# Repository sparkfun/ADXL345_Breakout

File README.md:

ADXL345 Breakout Board
===============================

[
*ADXL345 Breakout Board (SEN-09836)*](https://www.sparkfun.com/products/9836)

The ADXL345 is a small, thin, low power, 3-axis MEMS accelerometer with high resolution 913-bit) measurement at up to +-16g. 
Digital output data is formatted as 16-bit twos complement and is accessible through either an SPI or I2C digital interface. 

Repository Contents
-------------------

* **/Hardware** - All Eagle design files (.brd, .sch, .STL)
* **/Libraries** - All Arduino libraries and board examples
* **/Production** - Test bed files and production panel files

License Information
-------------------
The hardware is released under [Creative Commons ShareAlike 4.0 International](https://creativecommons.org/licenses/by-sa/4.0/).
The code is beerware; if you see me (or any other SparkFun employee) at the local, and you've found our code helpful, please buy us a round!

Distributed as-is; no warranty is given.

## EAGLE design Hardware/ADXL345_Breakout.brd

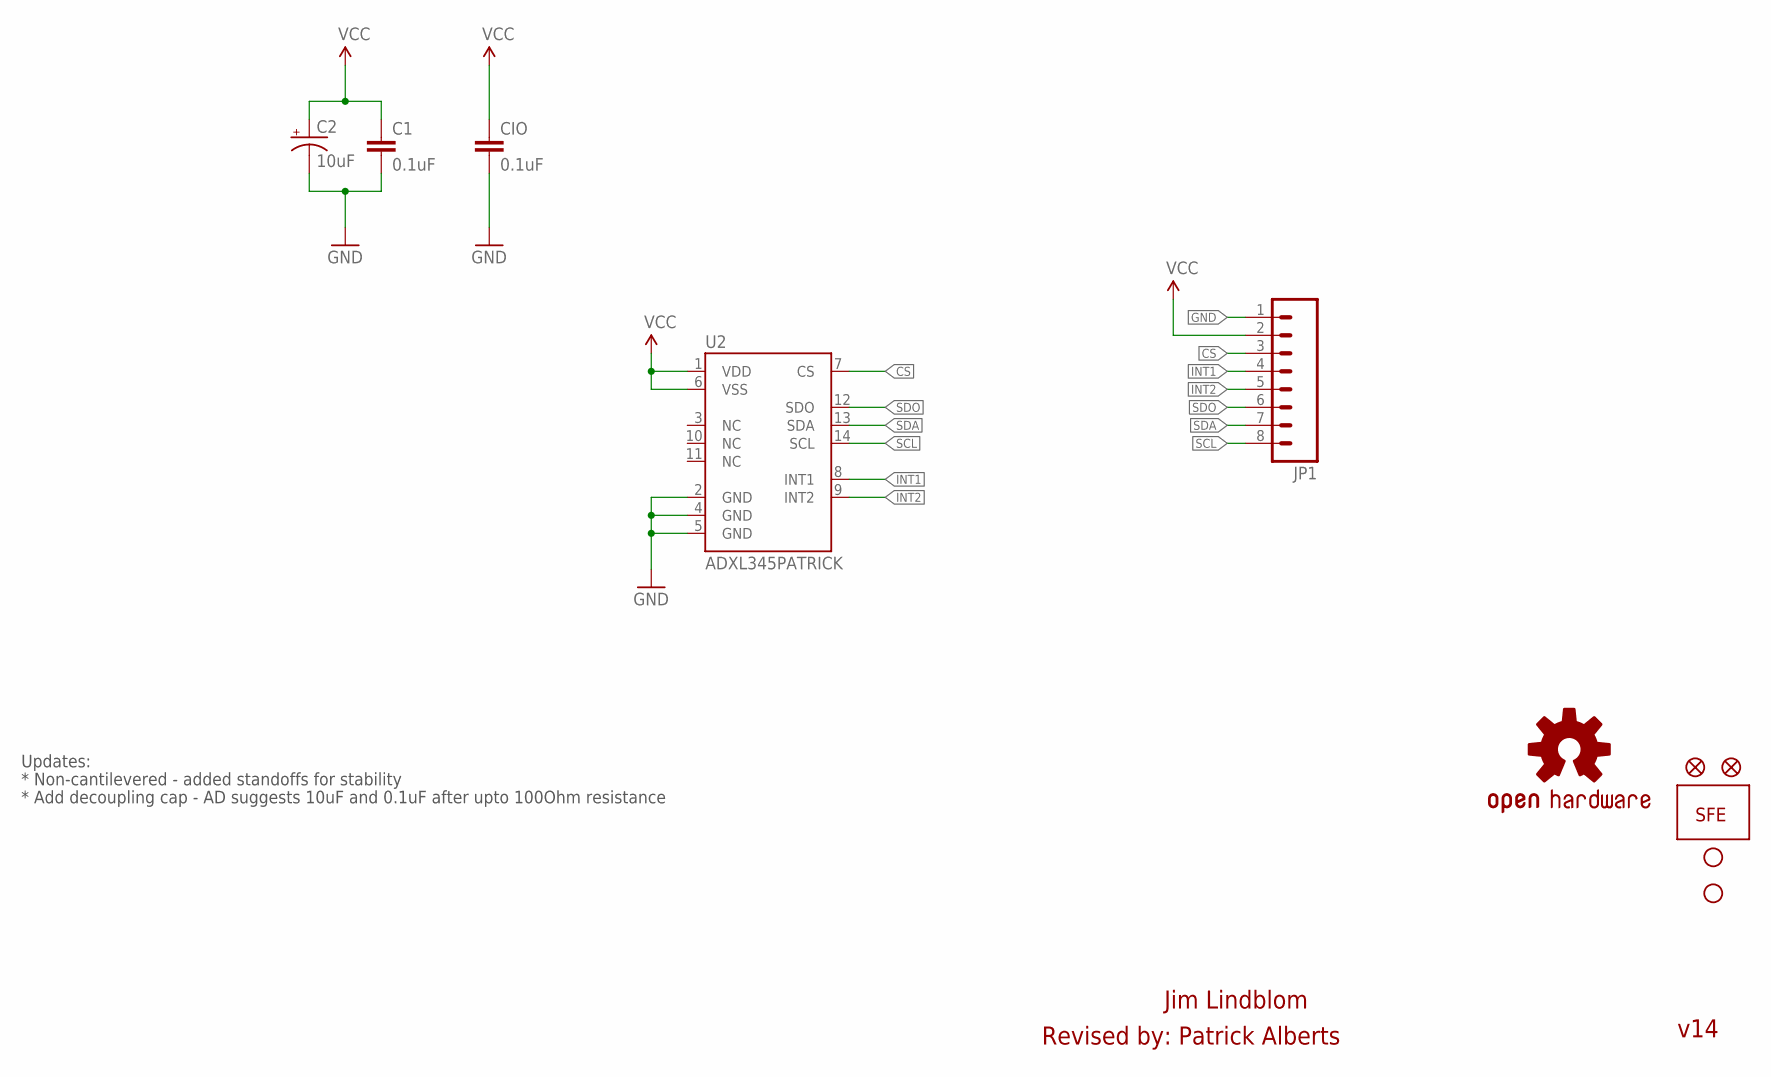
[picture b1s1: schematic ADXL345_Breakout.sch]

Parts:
C1: 0.1uF; 0603-CAP
C2: 10uF; EIA3216
CIO: 0.1uF; 0603-CAP
JP1: M08; 1X08
JP2, JP3: STAND-OFF
JP4, JP5: FIDUCIAL1X2; FIDUCIAL-1X2
U2: ADXL345PATRICK; LGA14_1:1_PATRICK
U$2: LOGO-SFENEW; SFE-NEW-WEBLOGO
U$3: OSHW-LOGOS; OSHW-LOGO-S

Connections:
CS: JP1.3, U2.7 (CS)
GND: C1.2, C2.C (-), CIO.2, JP1.1, U2.2 (GND), U2.4 (GND), U2.5 (GND)
INT1: JP1.4, U2.8 (INT1)
INT2: JP1.5, U2.9 (INT2)
SCL: JP1.8, U2.14 (SCL)
SDA: JP1.7, U2.13 (SDA)
SDO: JP1.6, U2.12 (SDO)
VCC: C1.1, C2.A (+), CIO.1, JP1.2, U2.1 (VDD), U2.6 (VSS)

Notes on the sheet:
Updates:
* Non-cantilevered - added standoffs for stability
* Add decoupling cap - AD suggests 10uF and 0.1uF after upto 100Ohm resistance
Jim Lindblom
Revised by: Patrick Alberts
v14

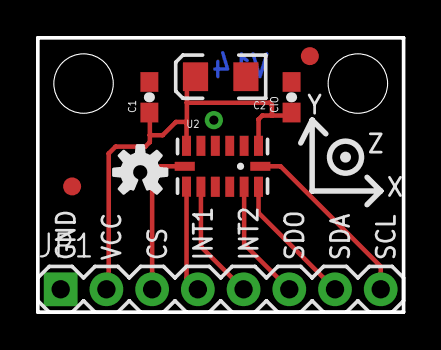
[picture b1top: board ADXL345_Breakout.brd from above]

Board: 2 copper layers, 20.3 x 15.2 mm, 11 parts (1 on the bottom side), 8 nets.

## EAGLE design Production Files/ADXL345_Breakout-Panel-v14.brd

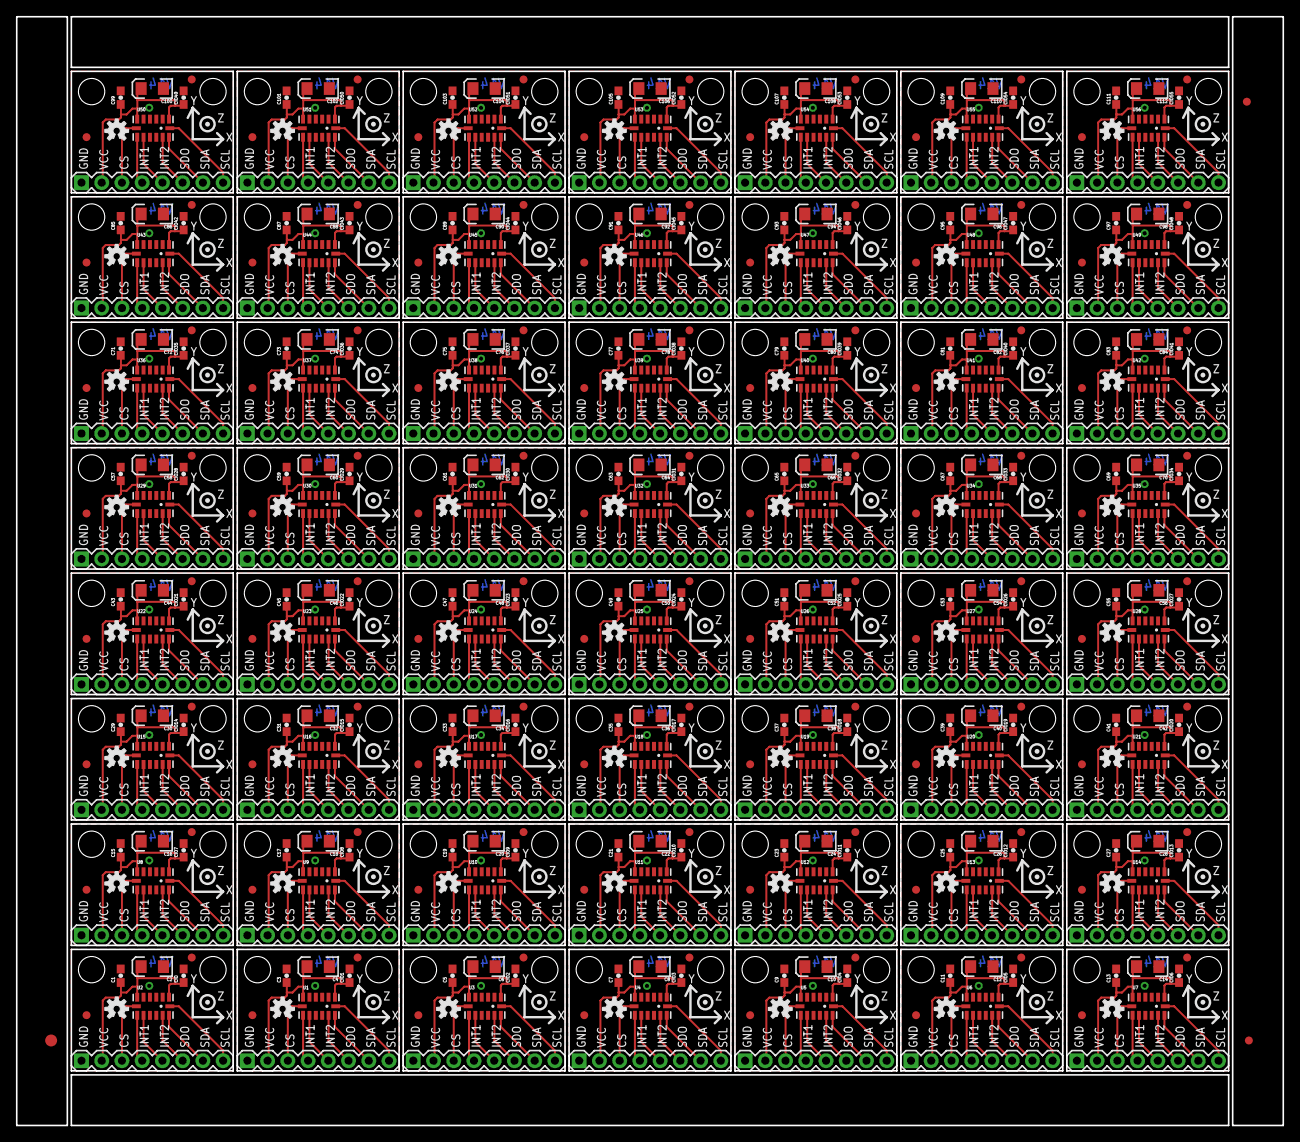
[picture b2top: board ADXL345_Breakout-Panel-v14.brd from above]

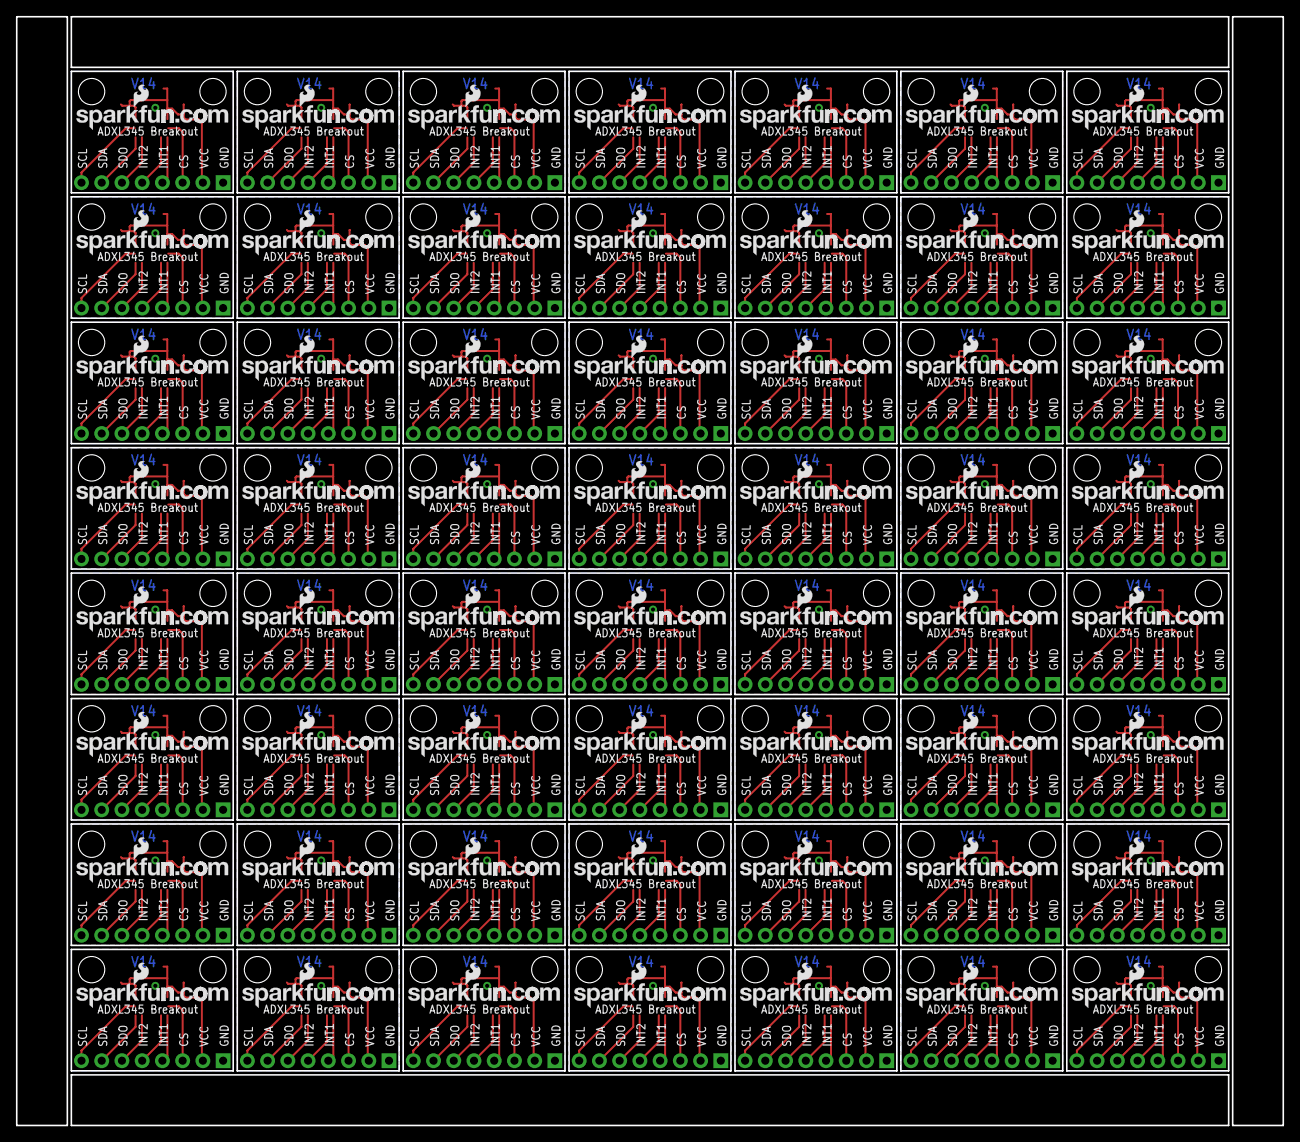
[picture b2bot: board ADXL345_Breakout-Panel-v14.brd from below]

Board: 2 copper layers, 159.0 x 139.2 mm, 619 parts (56 on the bottom side), 448 nets.

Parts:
C1, C3, C5, C7, C9, C11, C13, C15, C17, C19, C21, C23, C25, C27, C29, C31, C33, C35, C37, C39, C41, C43, C45, C47, C49, C51, C53, C55, C57, C59, C61, C63, C65, C67, C69, C71, C73, C75, C77, C79, C81, C83, C85, C87, C89, C91, C93, C95, C97, C99, C101, C103, C105, C107, C109, C111: 0.1uF; 0603-CAP
C2, C4, C6, C8, C10, C12, C14, C16, C18, C20, C22, C24, C26, C28, C30, C32, C34, C36, C38, C40, C42, C44, C46, C48, C50, C52, C54, C56, C58, C60, C62, C64, C66, C68, C70, C72, C74, C76, C78, C80, C82, C84, C86, C88, C90, C92, C94, C96, C98, C100, C102, C104, C106, C108, C110, C112: 10uF; EIA3216
CIO, CIO1, CIO2, CIO3, CIO4, CIO5, CIO6, CIO7, CIO8, CIO9, CIO10, CIO11, CIO12, CIO13, CIO14, CIO15, CIO16, CIO17, CIO18, CIO19, CIO20, CIO21, CIO22, CIO23, CIO24, CIO25, CIO26, CIO27, CIO28, CIO29, CIO30, CIO31, CIO32, CIO33, CIO34, CIO35, CIO36, CIO37, CIO38, CIO39, CIO40, CIO41, CIO42, CIO43, CIO44, CIO45, CIO46, CIO47, CIO48, CIO49, CIO50, CIO51, CIO52, CIO53, CIO54, CIO55: 0.1uF; 0603-CAP
E$1: FIDUCIAL-1.5X3
E$4, E$6: FIDUCIAL-1X2
JP1, JP6, JP11, JP16, JP21, JP26, JP31, JP36, JP41, JP46, JP51, JP56, JP61, JP66, JP71, JP76, JP81, JP86, JP91, JP96, JP101, JP106, JP111, JP116, JP121, JP126, JP131, JP136, JP141, JP146, JP151, JP156, JP161, JP166, JP171, JP176, JP181, JP186, JP191, JP196, JP201, JP206, JP211, JP216, JP221, JP226, JP231, JP236, JP241, JP246, JP251, JP256, JP261, JP266, JP271, JP276: 1X08
JP2, JP3, JP7, JP8, JP12, JP13, JP17, JP18, JP22, JP23, JP27, JP28, JP32, JP33, JP37, JP38, JP42, JP43, JP47, JP48, JP52, JP53, JP57, JP58, JP62, JP63, JP67, JP68, JP72, JP73, JP77, JP78, JP82, JP83, JP87, JP88, JP92, JP93, JP97, JP98, JP102, JP103, JP107, JP108, JP112, JP113, JP117, JP118, JP122, JP123, JP127, JP128, JP132, JP133, JP137, JP138, JP142, JP143, JP147, JP148, JP152, JP153, JP157, JP158, JP162, JP163, JP167, JP168, JP172, JP173, JP177, JP178, JP182, JP183, JP187, JP188, JP192, JP193, JP197, JP198, JP202, JP203, JP207, JP208, JP212, JP213, JP217, JP218, JP222, JP223, JP227, JP228, JP232, JP233, JP237, JP238, JP242, JP243, JP247, JP248, JP252, JP253, JP257, JP258, JP262, JP263, JP267, JP268, JP272, JP273, JP277, JP278: STAND-OFF
JP4, JP5, JP9, JP10, JP14, JP15, JP19, JP20, JP24, JP25, JP29, JP30, JP34, JP35, JP39, JP40, JP44, JP45, JP49, JP50, JP54, JP55, JP59, JP60, JP64, JP65, JP69, JP70, JP74, JP75, JP79, JP80, JP84, JP85, JP89, JP90, JP94, JP95, JP99, JP100, JP104, JP105, JP109, JP110, JP114, JP115, JP119, JP120, JP124, JP125, JP129, JP130, JP134, JP135, JP139, JP140, JP144, JP145, JP149, JP150, JP154, JP155, JP159, JP160, JP164, JP165, JP169, JP170, JP174, JP175, JP179, JP180, JP184, JP185, JP189, JP190, JP194, JP195, JP199, JP200, JP204, JP205, JP209, JP210, JP214, JP215, JP219, JP220, JP224, JP225, JP229, JP230, JP234, JP235, JP239, JP240, JP244, JP245, JP249, JP250, JP254, JP255, JP259, JP260, JP264, JP265, JP269, JP270, JP274, JP275, JP279, JP280: FIDUCIAL1X2; FIDUCIAL-1X2
U1, U2, U3, U4, U5, U6, U7, U8, U9, U10, U11, U12, U13, U14, U15, U16, U17, U18, U19, U20, U21, U22, U23, U24, U25, U26, U27, U28, U29, U30, U31, U32, U33, U34, U35, U36, U37, U38, U39, U40, U41, U42, U43, U44, U45, U46, U47, U48, U49, U50, U51, U52, U53, U54, U55, U56: ADXL345PATRICK; LGA14_1:1_PATRICK
U$1, U$2, U$5, U$7, U$9, U$11, U$13, U$15, U$17, U$19, U$21, U$23, U$25, U$27, U$29, U$31, U$33, U$35, U$37, U$39, U$41, U$43, U$45, U$47, U$49, U$51, U$53, U$55, U$57, U$59, U$61, U$63, U$65, U$67, U$69, U$71, U$73, U$75, U$77, U$79, U$81, U$83, U$85, U$87, U$89, U$91, U$93, U$95, U$97, U$99, U$101, U$103, U$105, U$107, U$109, U$111: LOGO-SFENEW; SFE-NEW-WEBLOGO
U$3, U$4, U$6, U$8, U$10, U$12, U$14, U$16, U$18, U$20, U$22, U$24, U$26, U$28, U$30, U$32, U$34, U$36, U$38, U$40, U$42, U$44, U$46, U$48, U$50, U$52, U$54, U$56, U$58, U$60, U$62, U$64, U$66, U$68, U$70, U$72, U$74, U$76, U$78, U$80, U$82, U$84, U$86, U$88, U$90, U$92, U$94, U$96, U$98, U$100, U$102, U$104, U$106, U$108, U$110, U$112: OSHW-LOGOS; OSHW-LOGO-S

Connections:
CS: JP1.3, U2.7
CS1: JP6.3, U1.7
CS2: JP11.3, U3.7
CS3: JP16.3, U4.7
CS4: JP21.3, U5.7
CS5: JP26.3, U6.7
CS6: JP31.3, U7.7
CS7: JP36.3, U8.7
CS8: JP41.3, U9.7
CS9: JP46.3, U10.7
CS10: JP51.3, U11.7
CS11: JP56.3, U12.7
CS12: JP61.3, U13.7
CS13: JP66.3, U14.7
CS14: JP71.3, U15.7
CS15: JP76.3, U16.7
CS16: JP81.3, U17.7
CS17: JP86.3, U18.7
CS18: JP91.3, U19.7
CS19: JP96.3, U20.7
CS20: JP101.3, U21.7
CS21: JP106.3, U22.7
CS22: JP111.3, U23.7
CS23: JP116.3, U24.7
CS24: JP121.3, U25.7
CS25: JP126.3, U26.7
CS26: JP131.3, U27.7
CS27: JP136.3, U28.7
CS28: JP141.3, U29.7
CS29: JP146.3, U30.7
CS30: JP151.3, U31.7
CS31: JP156.3, U32.7
CS32: JP161.3, U33.7
CS33: JP166.3, U34.7
CS34: JP171.3, U35.7
CS35: JP176.3, U36.7
CS36: JP181.3, U37.7
CS37: JP186.3, U38.7
CS38: JP191.3, U39.7
CS39: JP196.3, U40.7
CS40: JP201.3, U41.7
CS41: JP206.3, U42.7
CS42: JP211.3, U43.7
CS43: JP216.3, U44.7
CS44: JP221.3, U45.7
CS45: JP226.3, U46.7
CS46: JP231.3, U47.7
CS47: JP236.3, U48.7
CS48: JP241.3, U49.7
CS49: JP246.3, U50.7
CS50: JP251.3, U51.7
CS51: JP256.3, U52.7
CS52: JP261.3, U53.7
CS53: JP266.3, U54.7
CS54: JP271.3, U55.7
CS55: JP276.3, U56.7
GND: C1.2, C2.C, CIO.2, JP1.1, U2.2, U2.4, U2.5
GND1: C3.2, C4.C, CIO1.2, JP6.1, U1.2, U1.4, U1.5
GND2: C5.2, C6.C, CIO2.2, JP11.1, U3.2, U3.4, U3.5
GND3: C7.2, C8.C, CIO3.2, JP16.1, U4.2, U4.4, U4.5
GND4: C9.2, C10.C, CIO4.2, JP21.1, U5.2, U5.4, U5.5
GND5: C11.2, C12.C, CIO5.2, JP26.1, U6.2, U6.4, U6.5
GND6: C13.2, C14.C, CIO6.2, JP31.1, U7.2, U7.4, U7.5
GND7: C15.2, C16.C, CIO7.2, JP36.1, U8.2, U8.4, U8.5
GND8: C17.2, C18.C, CIO8.2, JP41.1, U9.2, U9.4, U9.5
GND9: C19.2, C20.C, CIO9.2, JP46.1, U10.2, U10.4, U10.5
GND10: C21.2, C22.C, CIO10.2, JP51.1, U11.2, U11.4, U11.5
GND11: C23.2, C24.C, CIO11.2, JP56.1, U12.2, U12.4, U12.5
GND12: C25.2, C26.C, CIO12.2, JP61.1, U13.2, U13.4, U13.5
GND13: C27.2, C28.C, CIO13.2, JP66.1, U14.2, U14.4, U14.5
GND14: C29.2, C30.C, CIO14.2, JP71.1, U15.2, U15.4, U15.5
GND15: C31.2, C32.C, CIO15.2, JP76.1, U16.2, U16.4, U16.5
GND16: C33.2, C34.C, CIO16.2, JP81.1, U17.2, U17.4, U17.5
GND17: C35.2, C36.C, CIO17.2, JP86.1, U18.2, U18.4, U18.5
GND18: C37.2, C38.C, CIO18.2, JP91.1, U19.2, U19.4, U19.5
GND19: C39.2, C40.C, CIO19.2, JP96.1, U20.2, U20.4, U20.5
GND20: C41.2, C42.C, CIO20.2, JP101.1, U21.2, U21.4, U21.5
GND21: C43.2, C44.C, CIO21.2, JP106.1, U22.2, U22.4, U22.5
GND22: C45.2, C46.C, CIO22.2, JP111.1, U23.2, U23.4, U23.5
GND23: C47.2, C48.C, CIO23.2, JP116.1, U24.2, U24.4, U24.5
GND24: C49.2, C50.C, CIO24.2, JP121.1, U25.2, U25.4, U25.5
GND25: C51.2, C52.C, CIO25.2, JP126.1, U26.2, U26.4, U26.5
GND26: C53.2, C54.C, CIO26.2, JP131.1, U27.2, U27.4, U27.5
GND27: C55.2, C56.C, CIO27.2, JP136.1, U28.2, U28.4, U28.5
GND28: C57.2, C58.C, CIO28.2, JP141.1, U29.2, U29.4, U29.5
GND29: C59.2, C60.C, CIO29.2, JP146.1, U30.2, U30.4, U30.5
GND30: C61.2, C62.C, CIO30.2, JP151.1, U31.2, U31.4, U31.5
GND31: C63.2, C64.C, CIO31.2, JP156.1, U32.2, U32.4, U32.5
GND32: C65.2, C66.C, CIO32.2, JP161.1, U33.2, U33.4, U33.5
GND33: C67.2, C68.C, CIO33.2, JP166.1, U34.2, U34.4, U34.5
GND34: C69.2, C70.C, CIO34.2, JP171.1, U35.2, U35.4, U35.5
GND35: C71.2, C72.C, CIO35.2, JP176.1, U36.2, U36.4, U36.5
GND36: C73.2, C74.C, CIO36.2, JP181.1, U37.2, U37.4, U37.5
GND37: C75.2, C76.C, CIO37.2, JP186.1, U38.2, U38.4, U38.5
GND38: C77.2, C78.C, CIO38.2, JP191.1, U39.2, U39.4, U39.5
GND39: C79.2, C80.C, CIO39.2, JP196.1, U40.2, U40.4, U40.5
GND40: C81.2, C82.C, CIO40.2, JP201.1, U41.2, U41.4, U41.5
GND41: C83.2, C84.C, CIO41.2, JP206.1, U42.2, U42.4, U42.5
GND42: C85.2, C86.C, CIO42.2, JP211.1, U43.2, U43.4, U43.5
GND43: C87.2, C88.C, CIO43.2, JP216.1, U44.2, U44.4, U44.5
GND44: C89.2, C90.C, CIO44.2, JP221.1, U45.2, U45.4, U45.5
GND45: C91.2, C92.C, CIO45.2, JP226.1, U46.2, U46.4, U46.5
GND46: C93.2, C94.C, CIO46.2, JP231.1, U47.2, U47.4, U47.5
GND47: C95.2, C96.C, CIO47.2, JP236.1, U48.2, U48.4, U48.5
GND48: C97.2, C98.C, CIO48.2, JP241.1, U49.2, U49.4, U49.5
GND49: C99.2, C100.C, CIO49.2, JP246.1, U50.2, U50.4, U50.5
GND50: C101.2, C102.C, CIO50.2, JP251.1, U51.2, U51.4, U51.5
GND51: C103.2, C104.C, CIO51.2, JP256.1, U52.2, U52.4, U52.5
GND52: C105.2, C106.C, CIO52.2, JP261.1, U53.2, U53.4, U53.5
GND53: C107.2, C108.C, CIO53.2, JP266.1, U54.2, U54.4, U54.5
GND54: C109.2, C110.C, CIO54.2, JP271.1, U55.2, U55.4, U55.5
GND55: C111.2, C112.C, CIO55.2, JP276.1, U56.2, U56.4, U56.5
INT1: JP1.4, U2.8
INT2: JP1.5, U2.9
INT3: JP6.5, U1.9
INT4: JP6.4, U1.8
INT5: JP11.5, U3.9
INT6: JP11.4, U3.8
INT7: JP16.5, U4.9
INT8: JP16.4, U4.8
INT9: JP21.5, U5.9
INT10: JP21.4, U5.8
INT11: JP26.5, U6.9
INT12: JP26.4, U6.8
INT13: JP31.5, U7.9
INT14: JP31.4, U7.8
INT15: JP36.5, U8.9
INT16: JP36.4, U8.8
INT17: JP41.5, U9.9
INT18: JP41.4, U9.8
INT19: JP46.5, U10.9
INT20: JP46.4, U10.8
INT21: JP51.5, U11.9
INT22: JP51.4, U11.8
INT23: JP56.5, U12.9
INT24: JP56.4, U12.8
INT25: JP61.5, U13.9
INT26: JP61.4, U13.8
INT27: JP66.5, U14.9
INT28: JP66.4, U14.8
INT29: JP71.5, U15.9
INT30: JP71.4, U15.8
INT31: JP76.5, U16.9
INT32: JP76.4, U16.8
INT33: JP81.5, U17.9
INT34: JP81.4, U17.8
INT35: JP86.5, U18.9
INT36: JP86.4, U18.8
INT37: JP91.5, U19.9
INT38: JP91.4, U19.8
INT39: JP96.5, U20.9
INT40: JP96.4, U20.8
INT41: JP101.5, U21.9
INT42: JP101.4, U21.8
INT43: JP106.5, U22.9
INT44: JP106.4, U22.8
INT45: JP111.5, U23.9
INT46: JP111.4, U23.8
INT47: JP116.5, U24.9
INT48: JP116.4, U24.8
INT49: JP121.5, U25.9
INT50: JP121.4, U25.8
INT51: JP126.5, U26.9
INT52: JP126.4, U26.8
INT53: JP131.5, U27.9
INT54: JP131.4, U27.8
INT55: JP136.5, U28.9
INT56: JP136.4, U28.8
INT57: JP141.5, U29.9
INT58: JP141.4, U29.8
INT59: JP146.5, U30.9
INT60: JP146.4, U30.8
INT61: JP151.5, U31.9
INT62: JP151.4, U31.8
INT63: JP156.5, U32.9
INT64: JP156.4, U32.8
INT65: JP161.5, U33.9
INT66: JP161.4, U33.8
INT67: JP166.5, U34.9
INT68: JP166.4, U34.8
INT69: JP171.5, U35.9
INT70: JP171.4, U35.8
INT71: JP176.5, U36.9
INT72: JP176.4, U36.8
INT73: JP181.5, U37.9
INT74: JP181.4, U37.8
INT75: JP186.5, U38.9
INT76: JP186.4, U38.8
INT77: JP191.5, U39.9
INT78: JP191.4, U39.8
INT79: JP196.5, U40.9
INT80: JP196.4, U40.8
INT81: JP201.5, U41.9
INT82: JP201.4, U41.8
INT83: JP206.5, U42.9
INT84: JP206.4, U42.8
INT85: JP211.5, U43.9
INT86: JP211.4, U43.8
INT87: JP216.5, U44.9
INT88: JP216.4, U44.8
INT89: JP221.5, U45.9
INT90: JP221.4, U45.8
INT91: JP226.5, U46.9
INT92: JP226.4, U46.8
INT93: JP231.5, U47.9
INT94: JP231.4, U47.8
INT95: JP236.5, U48.9
INT96: JP236.4, U48.8
INT97: JP241.5, U49.9
INT98: JP241.4, U49.8
INT99: JP246.5, U50.9
INT100: JP246.4, U50.8
INT101: JP251.5, U51.9
INT102: JP251.4, U51.8
INT103: JP256.5, U52.9
INT104: JP256.4, U52.8
INT105: JP261.5, U53.9
INT106: JP261.4, U53.8
INT107: JP266.5, U54.9
INT108: JP266.4, U54.8
INT109: JP271.5, U55.9
INT110: JP271.4, U55.8
INT111: JP276.5, U56.9
INT112: JP276.4, U56.8
SCL: JP1.8, U2.14
SCL1: JP6.8, U1.14
SCL2: JP11.8, U3.14
SCL3: JP16.8, U4.14
SCL4: JP21.8, U5.14
SCL5: JP26.8, U6.14
SCL6: JP31.8, U7.14
SCL7: JP36.8, U8.14
SCL8: JP41.8, U9.14
SCL9: JP46.8, U10.14
SCL10: JP51.8, U11.14
SCL11: JP56.8, U12.14
SCL12: JP61.8, U13.14
SCL13: JP66.8, U14.14
SCL14: JP71.8, U15.14
SCL15: JP76.8, U16.14
SCL16: JP81.8, U17.14
SCL17: JP86.8, U18.14
SCL18: JP91.8, U19.14
SCL19: JP96.8, U20.14
SCL20: JP101.8, U21.14
SCL21: JP106.8, U22.14
SCL22: JP111.8, U23.14
SCL23: JP116.8, U24.14
SCL24: JP121.8, U25.14
SCL25: JP126.8, U26.14
SCL26: JP131.8, U27.14
SCL27: JP136.8, U28.14
SCL28: JP141.8, U29.14
SCL29: JP146.8, U30.14
SCL30: JP151.8, U31.14
SCL31: JP156.8, U32.14
SCL32: JP161.8, U33.14
SCL33: JP166.8, U34.14
SCL34: JP171.8, U35.14
SCL35: JP176.8, U36.14
SCL36: JP181.8, U37.14
SCL37: JP186.8, U38.14
SCL38: JP191.8, U39.14
SCL39: JP196.8, U40.14
SCL40: JP201.8, U41.14
SCL41: JP206.8, U42.14
SCL42: JP211.8, U43.14
SCL43: JP216.8, U44.14
SCL44: JP221.8, U45.14
SCL45: JP226.8, U46.14
SCL46: JP231.8, U47.14
SCL47: JP236.8, U48.14
SCL48: JP241.8, U49.14
SCL49: JP246.8, U50.14
SCL50: JP251.8, U51.14
SCL51: JP256.8, U52.14
SCL52: JP261.8, U53.14
SCL53: JP266.8, U54.14
SCL54: JP271.8, U55.14
SCL55: JP276.8, U56.14
SDA: JP1.7, U2.13
SDA1: JP6.7, U1.13
SDA2: JP11.7, U3.13
SDA3: JP16.7, U4.13
SDA4: JP21.7, U5.13
SDA5: JP26.7, U6.13
SDA6: JP31.7, U7.13
SDA7: JP36.7, U8.13
SDA8: JP41.7, U9.13
SDA9: JP46.7, U10.13
SDA10: JP51.7, U11.13
SDA11: JP56.7, U12.13
SDA12: JP61.7, U13.13
SDA13: JP66.7, U14.13
SDA14: JP71.7, U15.13
SDA15: JP76.7, U16.13
SDA16: JP81.7, U17.13
SDA17: JP86.7, U18.13
SDA18: JP91.7, U19.13
SDA19: JP96.7, U20.13
SDA20: JP101.7, U21.13
SDA21: JP106.7, U22.13
SDA22: JP111.7, U23.13
SDA23: JP116.7, U24.13
SDA24: JP121.7, U25.13
SDA25: JP126.7, U26.13
SDA26: JP131.7, U27.13
SDA27: JP136.7, U28.13
SDA28: JP141.7, U29.13
SDA29: JP146.7, U30.13
SDA30: JP151.7, U31.13
SDA31: JP156.7, U32.13
SDA32: JP161.7, U33.13
SDA33: JP166.7, U34.13
SDA34: JP171.7, U35.13
SDA35: JP176.7, U36.13
SDA36: JP181.7, U37.13
SDA37: JP186.7, U38.13
SDA38: JP191.7, U39.13
SDA39: JP196.7, U40.13
SDA40: JP201.7, U41.13
SDA41: JP206.7, U42.13
SDA42: JP211.7, U43.13
SDA43: JP216.7, U44.13
SDA44: JP221.7, U45.13
SDA45: JP226.7, U46.13
SDA46: JP231.7, U47.13
SDA47: JP236.7, U48.13
SDA48: JP241.7, U49.13
SDA49: JP246.7, U50.13
SDA50: JP251.7, U51.13
SDA51: JP256.7, U52.13
SDA52: JP261.7, U53.13
SDA53: JP266.7, U54.13
SDA54: JP271.7, U55.13
SDA55: JP276.7, U56.13
SDO: JP1.6, U2.12
SDO1: JP6.6, U1.12
SDO2: JP11.6, U3.12
SDO3: JP16.6, U4.12
SDO4: JP21.6, U5.12
SDO5: JP26.6, U6.12
SDO6: JP31.6, U7.12
SDO7: JP36.6, U8.12
SDO8: JP41.6, U9.12
SDO9: JP46.6, U10.12
SDO10: JP51.6, U11.12
SDO11: JP56.6, U12.12
SDO12: JP61.6, U13.12
SDO13: JP66.6, U14.12
SDO14: JP71.6, U15.12
SDO15: JP76.6, U16.12
SDO16: JP81.6, U17.12
SDO17: JP86.6, U18.12
SDO18: JP91.6, U19.12
SDO19: JP96.6, U20.12
SDO20: JP101.6, U21.12
SDO21: JP106.6, U22.12
SDO22: JP111.6, U23.12
SDO23: JP116.6, U24.12
SDO24: JP121.6, U25.12
SDO25: JP126.6, U26.12
SDO26: JP131.6, U27.12
SDO27: JP136.6, U28.12
SDO28: JP141.6, U29.12
SDO29: JP146.6, U30.12
SDO30: JP151.6, U31.12
SDO31: JP156.6, U32.12
SDO32: JP161.6, U33.12
SDO33: JP166.6, U34.12
SDO34: JP171.6, U35.12
SDO35: JP176.6, U36.12
SDO36: JP181.6, U37.12
SDO37: JP186.6, U38.12
SDO38: JP191.6, U39.12
SDO39: JP196.6, U40.12
SDO40: JP201.6, U41.12
SDO41: JP206.6, U42.12
SDO42: JP211.6, U43.12
SDO43: JP216.6, U44.12
SDO44: JP221.6, U45.12
SDO45: JP226.6, U46.12
SDO46: JP231.6, U47.12
SDO47: JP236.6, U48.12
SDO48: JP241.6, U49.12
SDO49: JP246.6, U50.12
SDO50: JP251.6, U51.12
SDO51: JP256.6, U52.12
SDO52: JP261.6, U53.12
SDO53: JP266.6, U54.12
SDO54: JP271.6, U55.12
SDO55: JP276.6, U56.12
VCC: C1.1, C2.A, CIO.1, JP1.2, U2.1, U2.6
VCC1: C3.1, C4.A, CIO1.1, JP6.2, U1.1, U1.6
VCC2: C5.1, C6.A, CIO2.1, JP11.2, U3.1, U3.6
VCC3: C7.1, C8.A, CIO3.1, JP16.2, U4.1, U4.6
VCC4: C9.1, C10.A, CIO4.1, JP21.2, U5.1, U5.6
VCC5: C11.1, C12.A, CIO5.1, JP26.2, U6.1, U6.6
VCC6: C13.1, C14.A, CIO6.1, JP31.2, U7.1, U7.6
VCC7: C15.1, C16.A, CIO7.1, JP36.2, U8.1, U8.6
VCC8: C17.1, C18.A, CIO8.1, JP41.2, U9.1, U9.6
VCC9: C19.1, C20.A, CIO9.1, JP46.2, U10.1, U10.6
VCC10: C21.1, C22.A, CIO10.1, JP51.2, U11.1, U11.6
VCC11: C23.1, C24.A, CIO11.1, JP56.2, U12.1, U12.6
VCC12: C25.1, C26.A, CIO12.1, JP61.2, U13.1, U13.6
VCC13: C27.1, C28.A, CIO13.1, JP66.2, U14.1, U14.6
VCC14: C29.1, C30.A, CIO14.1, JP71.2, U15.1, U15.6
VCC15: C31.1, C32.A, CIO15.1, JP76.2, U16.1, U16.6
VCC16: C33.1, C34.A, CIO16.1, JP81.2, U17.1, U17.6
VCC17: C35.1, C36.A, CIO17.1, JP86.2, U18.1, U18.6
VCC18: C37.1, C38.A, CIO18.1, JP91.2, U19.1, U19.6
VCC19: C39.1, C40.A, CIO19.1, JP96.2, U20.1, U20.6
VCC20: C41.1, C42.A, CIO20.1, JP101.2, U21.1, U21.6
VCC21: C43.1, C44.A, CIO21.1, JP106.2, U22.1, U22.6
VCC22: C45.1, C46.A, CIO22.1, JP111.2, U23.1, U23.6
VCC23: C47.1, C48.A, CIO23.1, JP116.2, U24.1, U24.6
VCC24: C49.1, C50.A, CIO24.1, JP121.2, U25.1, U25.6
VCC25: C51.1, C52.A, CIO25.1, JP126.2, U26.1, U26.6
VCC26: C53.1, C54.A, CIO26.1, JP131.2, U27.1, U27.6
VCC27: C55.1, C56.A, CIO27.1, JP136.2, U28.1, U28.6
VCC28: C57.1, C58.A, CIO28.1, JP141.2, U29.1, U29.6
VCC29: C59.1, C60.A, CIO29.1, JP146.2, U30.1, U30.6
VCC30: C61.1, C62.A, CIO30.1, JP151.2, U31.1, U31.6
VCC31: C63.1, C64.A, CIO31.1, JP156.2, U32.1, U32.6
VCC32: C65.1, C66.A, CIO32.1, JP161.2, U33.1, U33.6
VCC33: C67.1, C68.A, CIO33.1, JP166.2, U34.1, U34.6
VCC34: C69.1, C70.A, CIO34.1, JP171.2, U35.1, U35.6
VCC35: C71.1, C72.A, CIO35.1, JP176.2, U36.1, U36.6
VCC36: C73.1, C74.A, CIO36.1, JP181.2, U37.1, U37.6
VCC37: C75.1, C76.A, CIO37.1, JP186.2, U38.1, U38.6
VCC38: C77.1, C78.A, CIO38.1, JP191.2, U39.1, U39.6
VCC39: C79.1, C80.A, CIO39.1, JP196.2, U40.1, U40.6
VCC40: C81.1, C82.A, CIO40.1, JP201.2, U41.1, U41.6
VCC41: C83.1, C84.A, CIO41.1, JP206.2, U42.1, U42.6
VCC42: C85.1, C86.A, CIO42.1, JP211.2, U43.1, U43.6
VCC43: C87.1, C88.A, CIO43.1, JP216.2, U44.1, U44.6
VCC44: C89.1, C90.A, CIO44.1, JP221.2, U45.1, U45.6
VCC45: C91.1, C92.A, CIO45.1, JP226.2, U46.1, U46.6
VCC46: C93.1, C94.A, CIO46.1, JP231.2, U47.1, U47.6
VCC47: C95.1, C96.A, CIO47.1, JP236.2, U48.1, U48.6
VCC48: C97.1, C98.A, CIO48.1, JP241.2, U49.1, U49.6
VCC49: C99.1, C100.A, CIO49.1, JP246.2, U50.1, U50.6
VCC50: C101.1, C102.A, CIO50.1, JP251.2, U51.1, U51.6
VCC51: C103.1, C104.A, CIO51.1, JP256.2, U52.1, U52.6
VCC52: C105.1, C106.A, CIO52.1, JP261.2, U53.1, U53.6
VCC53: C107.1, C108.A, CIO53.1, JP266.2, U54.1, U54.6
VCC54: C109.1, C110.A, CIO54.1, JP271.2, U55.1, U55.6
VCC55: C111.1, C112.A, CIO55.1, JP276.2, U56.1, U56.6

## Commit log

2013-07-25 Initial Commit
    Initial commit of V13, next up revisions.
2013-08-08 0402 to 0603, Trace Re-routing and new ADXL PK
    Changed the 0402 caps to 0603 and created a new ADXL345 package. Minor
    trace re routing and added a new revision code as well as the Open
    Hardware logo.
2013-08-08 Removed Via and moved a via
2013-08-08 Moved OSH logo, cleaned up routes
2013-08-12 Schematic Change, CAP Names, Package Move
    Updated to Frame Letter for the Schematic, Changed Caps names to C2, C1
    and Moved the ADXL345 package to make more room for the 10uf Cap.
2013-08-23 Added fiducials
    Forgot to put these on the protos, fiducials now added.
2013-09-11 Fixed air wire
    Fixed air wire
2013-09-11 Panel Created
2013-11-27 Readme updated
2014-02-06 Updating README, versions on board files
2025-06-27 Update README.md
    Updating link

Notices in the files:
parts and their libraries:
SparkFun-Aesthetics: Licensing: CC v3.0 Share-Alike You are welcome to use this library for commercial purposes.
SparkFun-Aesthetics: Released under the Creative Commons
SparkFun-Aesthetics: http://creativecommons.org/licenses/by-sa/3.0
